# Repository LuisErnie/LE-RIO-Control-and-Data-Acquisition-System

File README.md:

# Industrial Control and Data Acquisition System

LOW-level Engineering modular data acquisition and control hardware platform. The system is a combination of a power supply, integrated I/O, integrated communications interfaces, signal and isolation to interface with expansion modules to tailor it to the application and an FPGA as a main controller.

The system is designed around the DE-10 Nano FPGA board from Terasic, although any embedded controller can be adapted to interface with the two 40-pin IDC connectors.

## Features
- Fully Modular I/O interface.
- Expansion Ports with 24V and 5V Power and Signal Isolation.
- Single 24V Power Supply Required.
- Multiple Communications Interfaces Supported, RS-485, CAN, RS-232, USB, SPI and I2C.

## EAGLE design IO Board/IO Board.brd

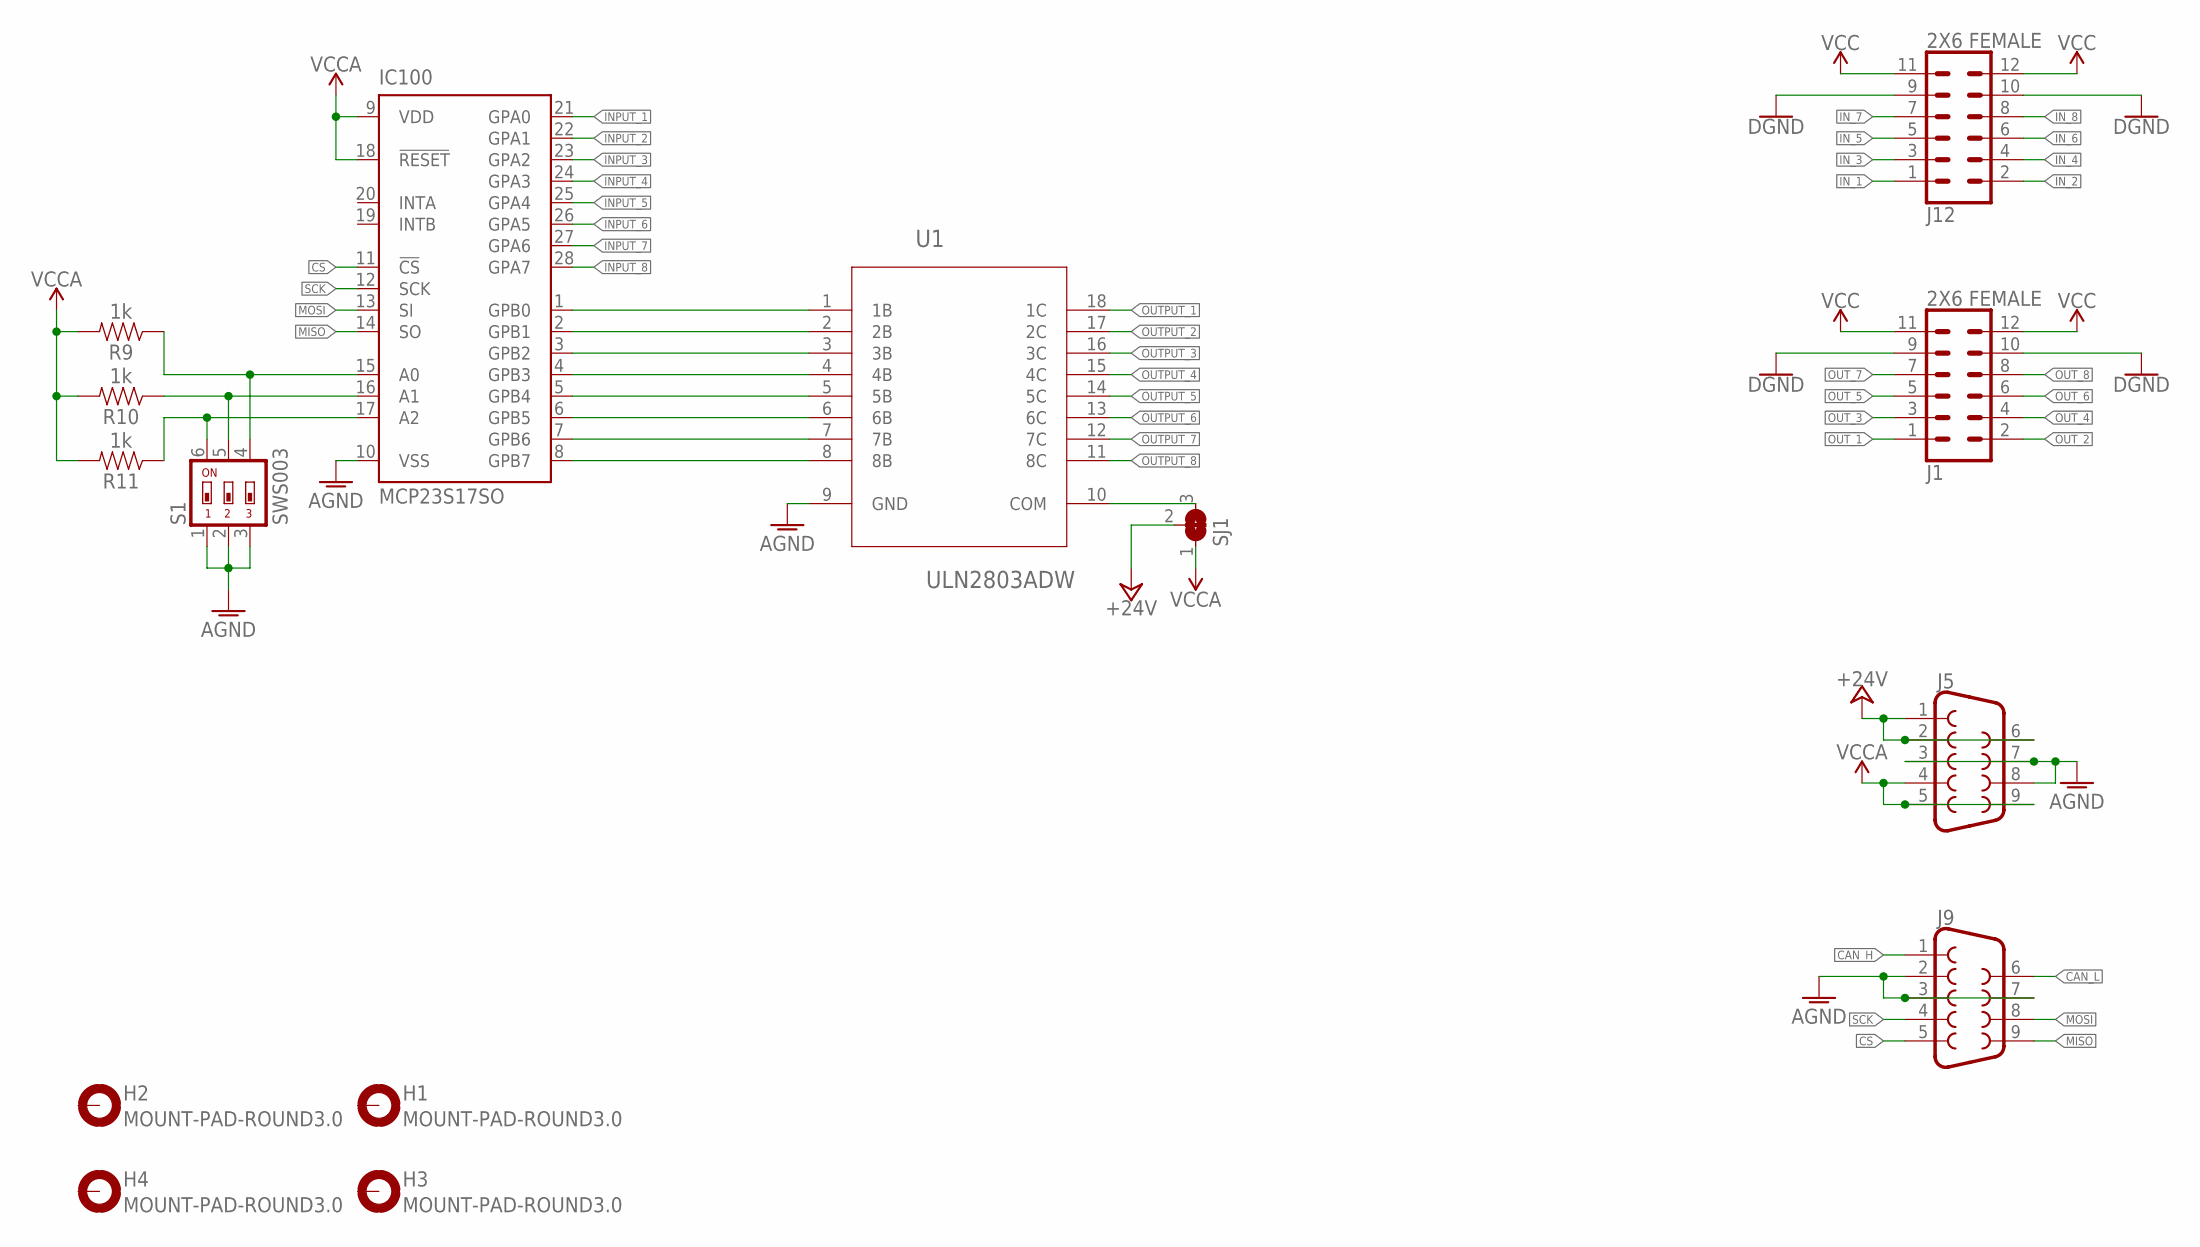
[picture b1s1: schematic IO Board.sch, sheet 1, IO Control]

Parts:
H1, H2, H3, H4: MOUNT-PAD-ROUND3.0; 3,0-PAD
IC100: MCP23S17SO; SO28W
J1, J12: 2X6 FEMALE; 2X6
J5, J9: DB9FEMALE; DB9
R9, R10, R11: 1k; 0805
S1: SWS003; SMS-003
SJ1: SOLDERJUMPER_2WAY; SOLDERJUMPER_2WAY_OPEN_NOPASTE
U1: ULN2803ADW; SOIC127P1030X265-18N

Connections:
+24V: J5.1, J5.2, J5.6, SJ1.2; also elsewhere on the board
AGND: IC100.10 (VSS), J5.3, J5.7, J5.8, J9.2, J9.3, J9.7, S1.1, S1.2, S1.3, U1.9 (GND); also elsewhere on the board
CAN_H: J9.1
CAN_L: J9.6
CS: IC100.11 (!CS), J9.5
GND: J1.9, J1.10, J12.9, J12.10; also elsewhere on the board
INPUT_1: IC100.21 (GPA0); also elsewhere on the board
INPUT_2: IC100.22 (GPA1); also elsewhere on the board
INPUT_3: IC100.23 (GPA2); also elsewhere on the board
INPUT_4: IC100.24 (GPA3); also elsewhere on the board
INPUT_5: IC100.25 (GPA4); also elsewhere on the board
INPUT_6: IC100.26 (GPA5); also elsewhere on the board
INPUT_7: IC100.27 (GPA6); also elsewhere on the board
INPUT_8: IC100.28 (GPA7); also elsewhere on the board
IN_1: J12.1; also elsewhere on the board
IN_2: J12.2; also elsewhere on the board
IN_3: J12.3; also elsewhere on the board
IN_4: J12.4; also elsewhere on the board
IN_5: J12.5; also elsewhere on the board
IN_6: J12.6; also elsewhere on the board
IN_7: J12.7; also elsewhere on the board
IN_8: J12.8; also elsewhere on the board
MISO: IC100.14 (SO), J9.9
MOSI: IC100.13 (SI), J9.8
unnamed: IC100.1 (GPB0), U1.1 (1B)
unnamed: IC100.3 (GPB2), U1.3 (3B)
unnamed: IC100.2 (GPB1), U1.2 (2B)
unnamed: IC100.4 (GPB3), U1.4 (4B)
unnamed: SJ1.3, U1.10 (COM)
unnamed: IC100.5 (GPB4), U1.5 (5B)
unnamed: IC100.7 (GPB6), U1.7 (7B)
unnamed: IC100.6 (GPB5), U1.6 (6B)
unnamed: IC100.8 (GPB7), U1.8 (8B)
unnamed: IC100.15 (A0), R9.1, S1.4
unnamed: IC100.16 (A1), R10.1, S1.5
unnamed: IC100.17 (A2), R11.1, S1.6
OUTPUT_1: U1.18 (1C); also elsewhere on the board
OUTPUT_2: U1.17 (2C); also elsewhere on the board
OUTPUT_3: U1.16 (3C); also elsewhere on the board
OUTPUT_4: U1.15 (4C); also elsewhere on the board
OUTPUT_5: U1.14 (5C); also elsewhere on the board
OUTPUT_6: U1.13 (6C); also elsewhere on the board
OUTPUT_7: U1.12 (7C); also elsewhere on the board
OUTPUT_8: U1.11 (8C); also elsewhere on the board
OUT_1: J1.1; also elsewhere on the board
OUT_2: J1.2; also elsewhere on the board
OUT_3: J1.3; also elsewhere on the board
OUT_4: J1.4; also elsewhere on the board
OUT_5: J1.5; also elsewhere on the board
OUT_6: J1.6; also elsewhere on the board
OUT_7: J1.7; also elsewhere on the board
OUT_8: J1.8; also elsewhere on the board
SCK: IC100.12 (SCK), J9.4
VCC: J1.11, J1.12, J12.11, J12.12; also elsewhere on the board
VCCA: IC100.9 (VDD), IC100.18 (!RESET), J5.4, J5.5, J5.9, R9.2, R10.2, R11.2, SJ1.1; also elsewhere on the board

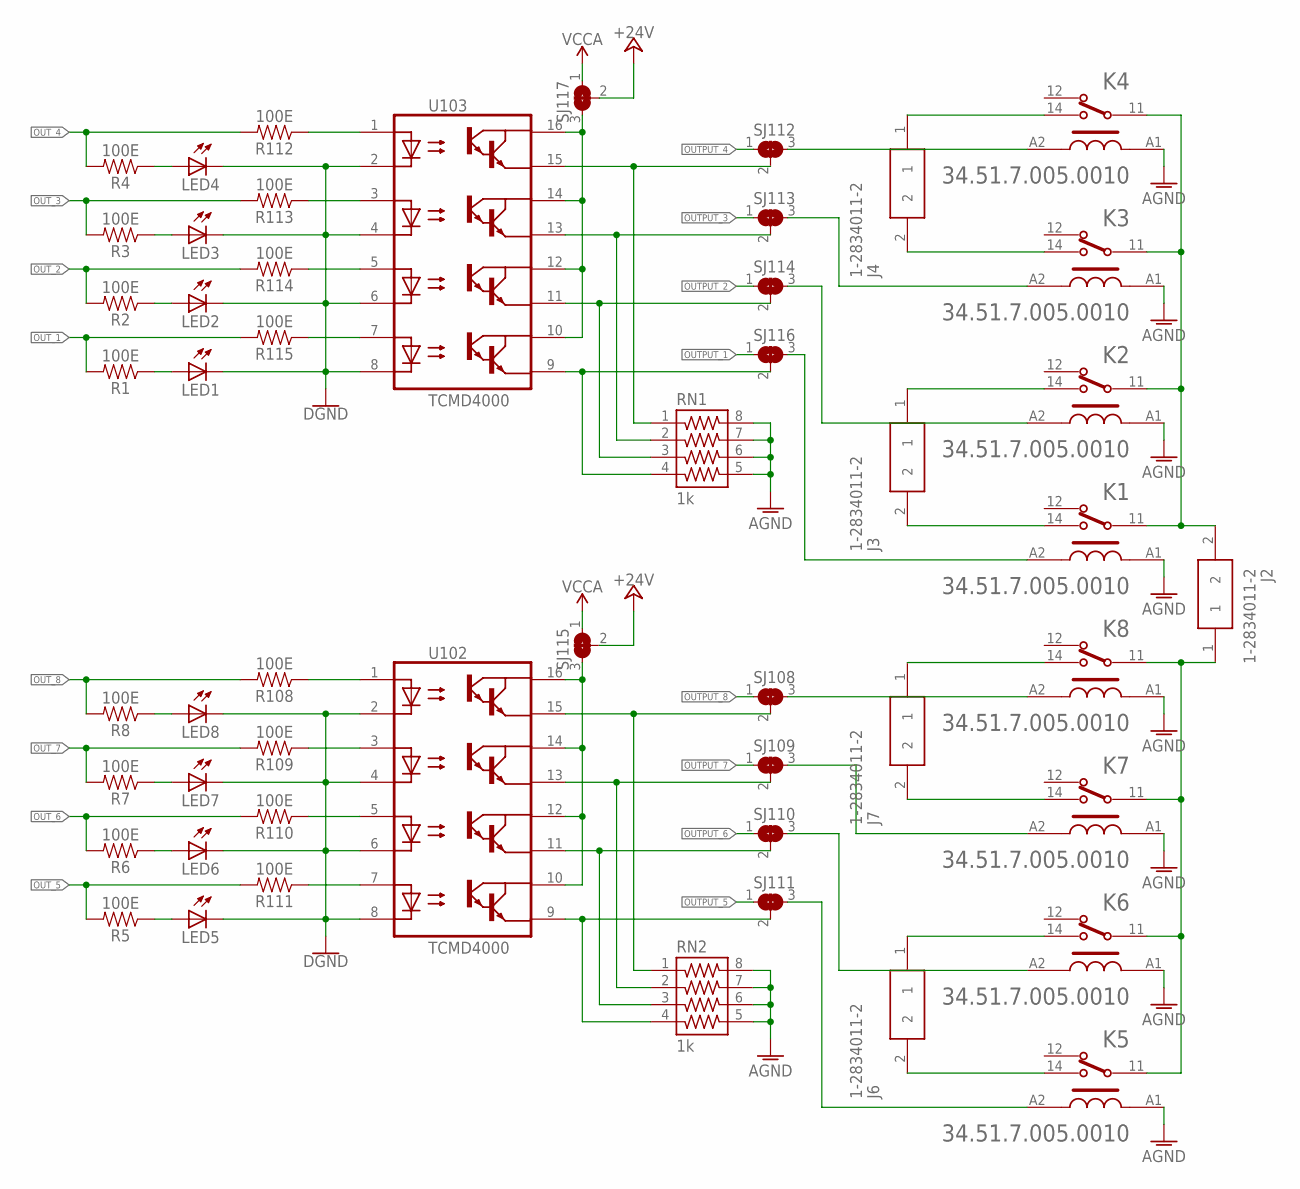
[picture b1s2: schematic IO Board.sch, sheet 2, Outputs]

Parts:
J2, J3, J4, J6, J7: 1-2834011-2; 128340112
K1, K2, K3, K4, K5, K6, K7, K8: FINDER_34.51.7.005.0010FINDER_34.51.7.005.0010_0_0; FINDER_34.51.7.005.0010_0
LED1, LED2, LED3, LED4, LED5, LED6, LED7, LED8: LEDCHIP-LED0805; CHIP-LED0805
R1, R2, R3, R4, R5, R6, R7, R8, R108, R109, R110, R111, R112, R113, R114, R115: 100E; 0805
RN1, RN2: 1k; 743-8NS
SJ108, SJ109, SJ110, SJ111, SJ112, SJ113, SJ114, SJ115, SJ116, SJ117: SOLDERJUMPER_2WAY; SOLDERJUMPER_2WAY_OPEN_NOPASTE
U102, U103: TCMD4000; SOIC127P686X201-16N

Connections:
+24V: SJ115.2, SJ117.2; also elsewhere on the board
AGND: K1.A1, K2.A1, K3.A1, K4.A1, K5.A1, K6.A1, K7.A1, K8.A1, RN1.5, RN1.6, RN1.7, RN1.8, RN2.5, RN2.6, RN2.7, RN2.8; also elsewhere on the board
GND: LED1.C, LED2.C, LED3.C, LED4.C, LED5.C, LED6.C, LED7.C, LED8.C, U102.2 (C1), U102.4 (C2), U102.6 (C3), U102.8 (C4), U103.2 (C1), U103.4 (C2), U103.6 (C3), U103.8 (C4); also elsewhere on the board
unnamed: K3.A2, SJ113.3
unnamed: RN1.3, SJ114.2, U103.11 (E3)
unnamed: RN1.4, SJ116.2, U103.9 (E4)
unnamed: K8.A2, SJ108.3
unnamed: K7.A2, SJ109.3
unnamed: RN2.3, SJ110.2, U102.11 (E3)
unnamed: RN2.4, SJ111.2, U102.9 (E4)
unnamed: K4.A2, SJ112.3
unnamed: LED4.A, R4.1
unnamed: LED8.A, R8.1
unnamed: LED7.A, R7.1
unnamed: LED6.A, R6.1
unnamed: LED5.A, R5.1
unnamed: R108.1, U102.1 (A1)
unnamed: R109.1, U102.3 (A2)
unnamed: R110.1, U102.5 (A3)
unnamed: R111.1, U102.7 (A4)
unnamed: SJ115.3, U102.10 (CO4), U102.12 (CO3), U102.14 (CO2), U102.16 (CO1)
unnamed: RN2.2, SJ109.2, U102.13 (E2)
unnamed: LED3.A, R3.1
unnamed: RN2.1, SJ108.2, U102.15 (E1)
unnamed: K5.A2, SJ111.3
unnamed: J4.1, K4.14
unnamed: J4.2, K3.14
unnamed: J3.1, K2.14
unnamed: LED2.A, R2.1
unnamed: LED1.A, R1.1
unnamed: J3.2, K1.14
unnamed: J2.1, K5.11, K6.11, K7.11, K8.11
unnamed: R112.1, U103.1 (A1)
unnamed: J7.1, K8.14
unnamed: J2.2, K1.11, K2.11, K3.11, K4.11
unnamed: K6.A2, SJ110.3
unnamed: J7.2, K7.14
unnamed: J6.1, K6.14
unnamed: K2.A2, SJ114.3
unnamed: R113.1, U103.3 (A2)
unnamed: R114.1, U103.5 (A3)
unnamed: R115.1, U103.7 (A4)
unnamed: SJ117.3, U103.10 (CO4), U103.12 (CO3), U103.14 (CO2), U103.16 (CO1)
unnamed: RN1.2, SJ113.2, U103.13 (E2)
unnamed: RN1.1, SJ112.2, U103.15 (E1)
unnamed: K1.A2, SJ116.3
unnamed: J6.2, K5.14
OUTPUT_1: SJ116.1; also elsewhere on the board
OUTPUT_2: SJ114.1; also elsewhere on the board
OUTPUT_3: SJ113.1; also elsewhere on the board
OUTPUT_4: SJ112.1; also elsewhere on the board
OUTPUT_5: SJ111.1; also elsewhere on the board
OUTPUT_6: SJ110.1; also elsewhere on the board
OUTPUT_7: SJ109.1; also elsewhere on the board
OUTPUT_8: SJ108.1; also elsewhere on the board
OUT_1: R1.2, R115.2; also elsewhere on the board
OUT_2: R2.2, R114.2; also elsewhere on the board
OUT_3: R3.2, R113.2; also elsewhere on the board
OUT_4: R4.2, R112.2; also elsewhere on the board
OUT_5: R5.2, R111.2; also elsewhere on the board
OUT_6: R6.2, R110.2; also elsewhere on the board
OUT_7: R7.2, R109.2; also elsewhere on the board
OUT_8: R8.2, R108.2; also elsewhere on the board
VCCA: SJ115.1, SJ117.1; also elsewhere on the board

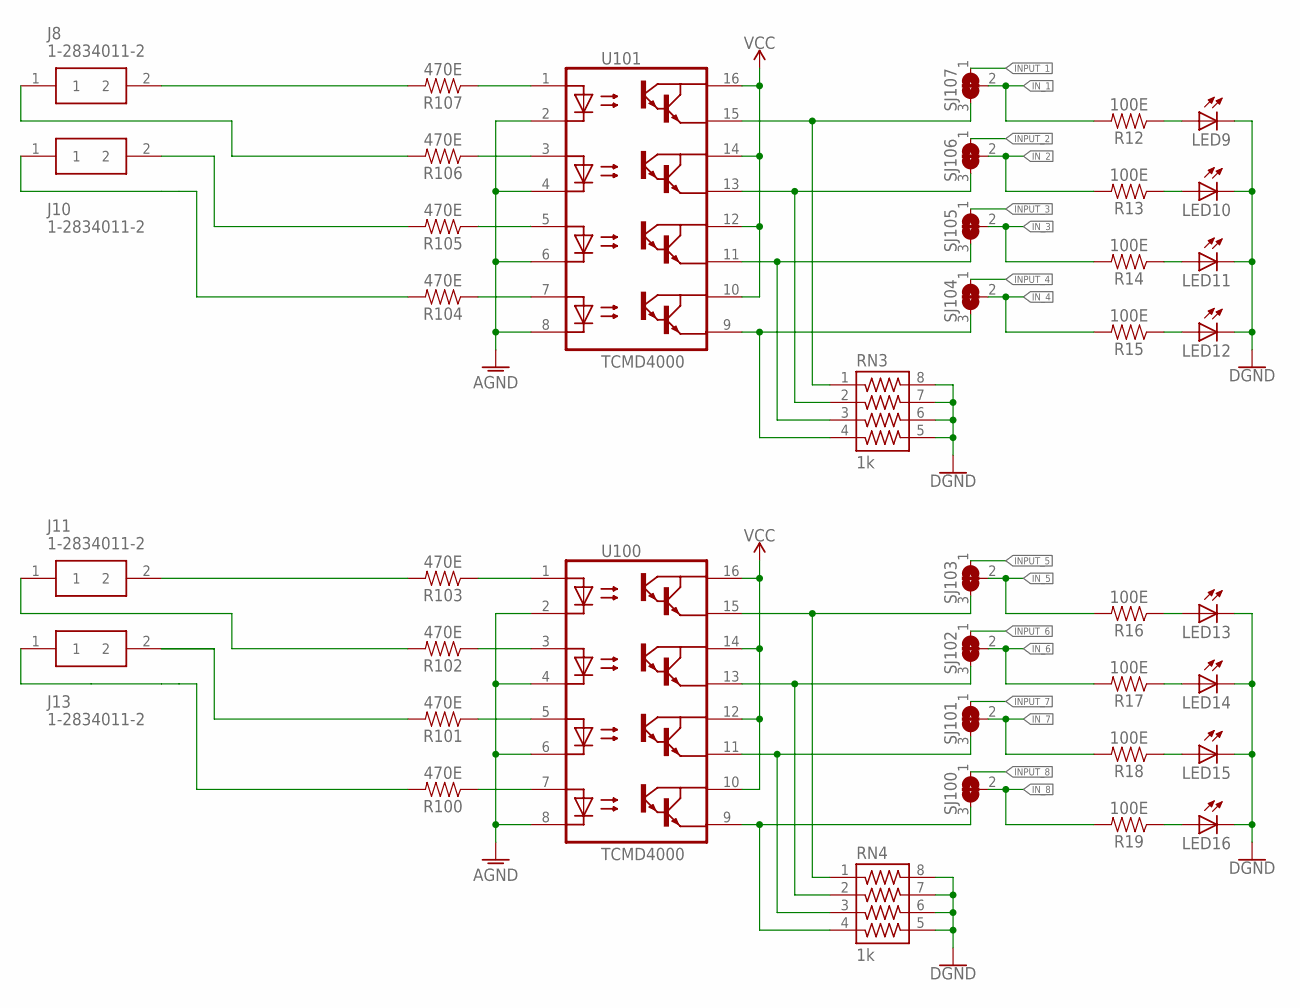
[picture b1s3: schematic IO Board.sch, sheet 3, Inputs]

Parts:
J8, J10, J11, J13: 1-2834011-2; 128340112
LED9, LED10, LED11, LED12, LED13, LED14, LED15, LED16: LEDCHIP-LED0805; CHIP-LED0805
R12, R13, R14, R15, R16, R17, R18, R19: 100E; 0805
R100, R101, R102, R103, R104, R105, R106, R107: 470E; 0805
RN3, RN4: 1k; 743-8NS
SJ100, SJ101, SJ102, SJ103, SJ104, SJ105, SJ106, SJ107: SOLDERJUMPER_2WAY; SOLDERJUMPER_2WAY_OPEN_NOPASTE
U100, U101: TCMD4000; SOIC127P686X201-16N

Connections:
AGND: U100.2 (C1), U100.4 (C2), U100.6 (C3), U100.8 (C4), U101.2 (C1), U101.4 (C2), U101.6 (C3), U101.8 (C4); also elsewhere on the board
GND: LED9.C, LED10.C, LED11.C, LED12.C, LED13.C, LED14.C, LED15.C, LED16.C, RN3.5, RN3.6, RN3.7, RN3.8, RN4.5, RN4.6, RN4.7, RN4.8; also elsewhere on the board
INPUT_1: SJ107.1; also elsewhere on the board
INPUT_2: SJ106.1; also elsewhere on the board
INPUT_3: SJ105.1; also elsewhere on the board
INPUT_4: SJ104.1; also elsewhere on the board
INPUT_5: SJ103.1; also elsewhere on the board
INPUT_6: SJ102.1; also elsewhere on the board
INPUT_7: SJ101.1; also elsewhere on the board
INPUT_8: SJ100.1; also elsewhere on the board
IN_1: R12.2, SJ107.2; also elsewhere on the board
IN_2: R13.2, SJ106.2; also elsewhere on the board
IN_3: R14.2, SJ105.2; also elsewhere on the board
IN_4: R15.2, SJ104.2; also elsewhere on the board
IN_5: R16.2, SJ103.2; also elsewhere on the board
IN_6: R17.2, SJ102.2; also elsewhere on the board
IN_7: R18.2, SJ101.2; also elsewhere on the board
IN_8: R19.2, SJ100.2; also elsewhere on the board
unnamed: LED9.A, R12.1
unnamed: LED10.A, R13.1
unnamed: LED11.A, R14.1
unnamed: LED12.A, R15.1
unnamed: R107.1, U101.1 (A1)
unnamed: R106.1, U101.3 (A2)
unnamed: J8.1, R106.2
unnamed: J13.2, R101.2
unnamed: R105.1, U101.5 (A3)
unnamed: R104.1, U101.7 (A4)
unnamed: LED13.A, R16.1
unnamed: RN3.2, SJ106.3, U101.13 (E2)
unnamed: RN3.1, SJ107.3, U101.15 (E1)
unnamed: LED14.A, R17.1
unnamed: LED15.A, R18.1
unnamed: LED16.A, R19.1
unnamed: R103.1, U100.1 (A1)
unnamed: R102.1, U100.3 (A2)
unnamed: R101.1, U100.5 (A3)
unnamed: R100.1, U100.7 (A4)
unnamed: RN4.2, SJ102.3, U100.13 (E2)
unnamed: RN4.1, SJ103.3, U100.15 (E1)
unnamed: RN4.3, SJ101.3, U100.11 (E3)
unnamed: RN4.4, SJ100.3, U100.9 (E4)
unnamed: J8.2, R107.2
unnamed: J10.2, R105.2
unnamed: J10.1, R104.2
unnamed: RN3.3, SJ105.3, U101.11 (E3)
unnamed: RN3.4, SJ104.3, U101.9 (E4)
unnamed: J11.2, R103.2
unnamed: J11.1, R102.2
unnamed: J13.1, R100.2
VCC: U100.10 (CO4), U100.12 (CO3), U100.14 (CO2), U100.16 (CO1), U101.10 (CO4), U101.12 (CO3), U101.14 (CO2), U101.16 (CO1); also elsewhere on the board

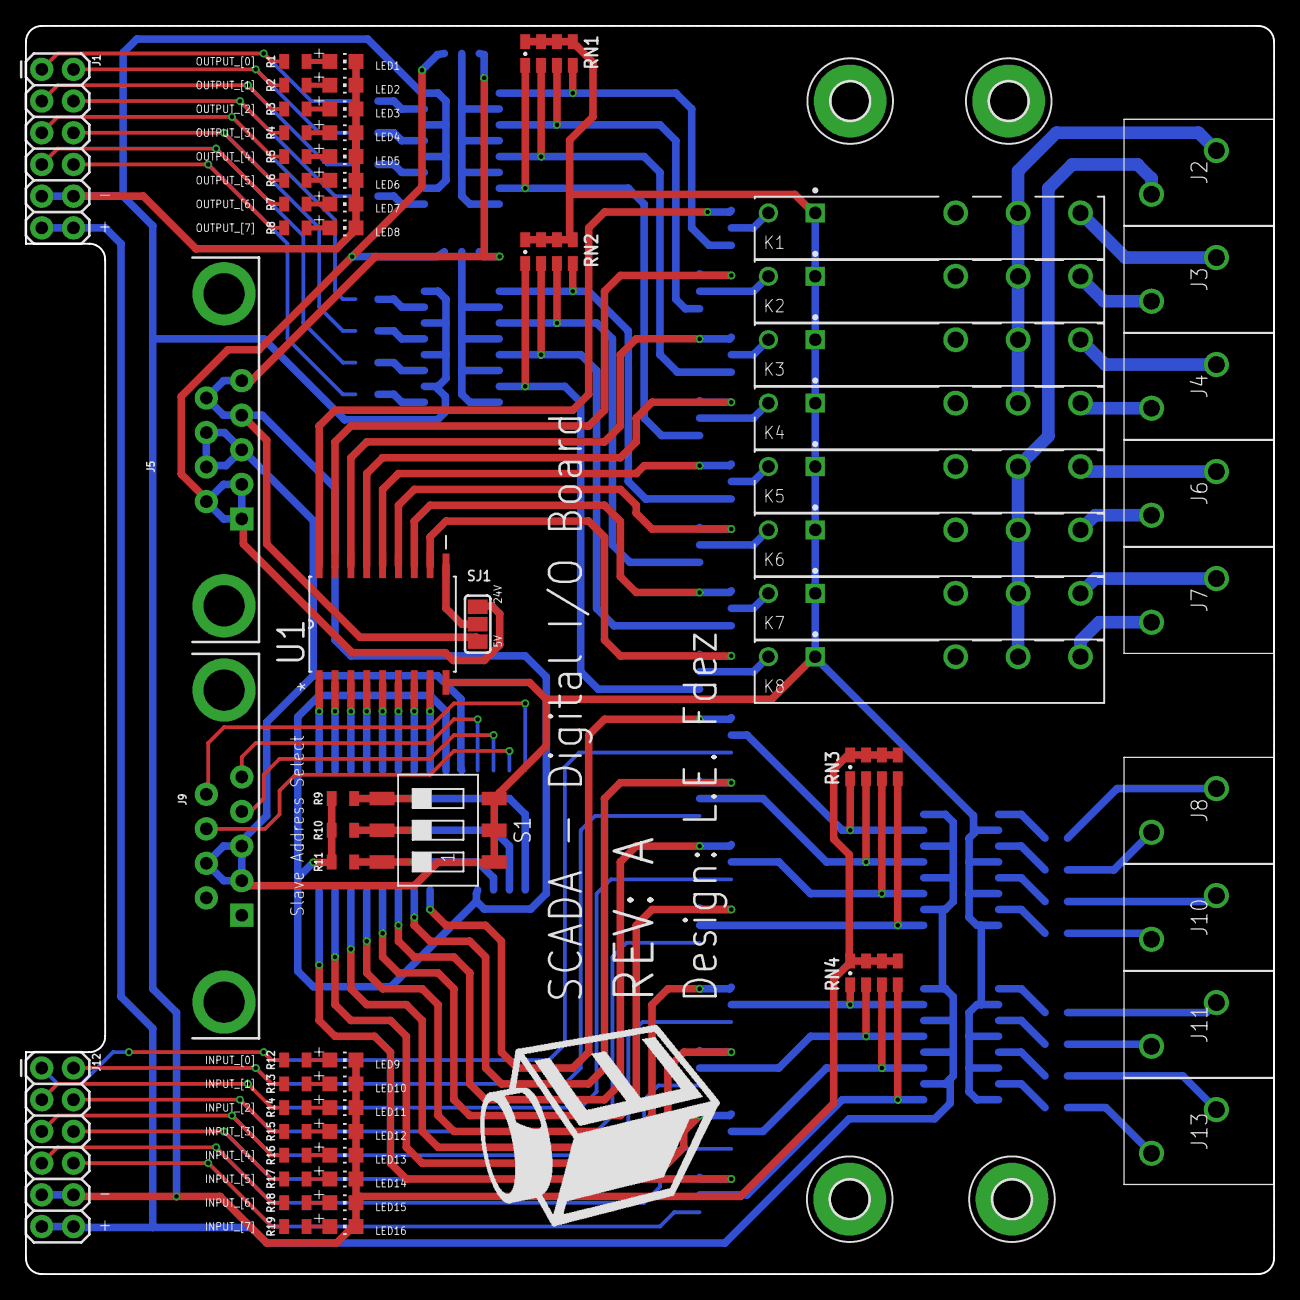
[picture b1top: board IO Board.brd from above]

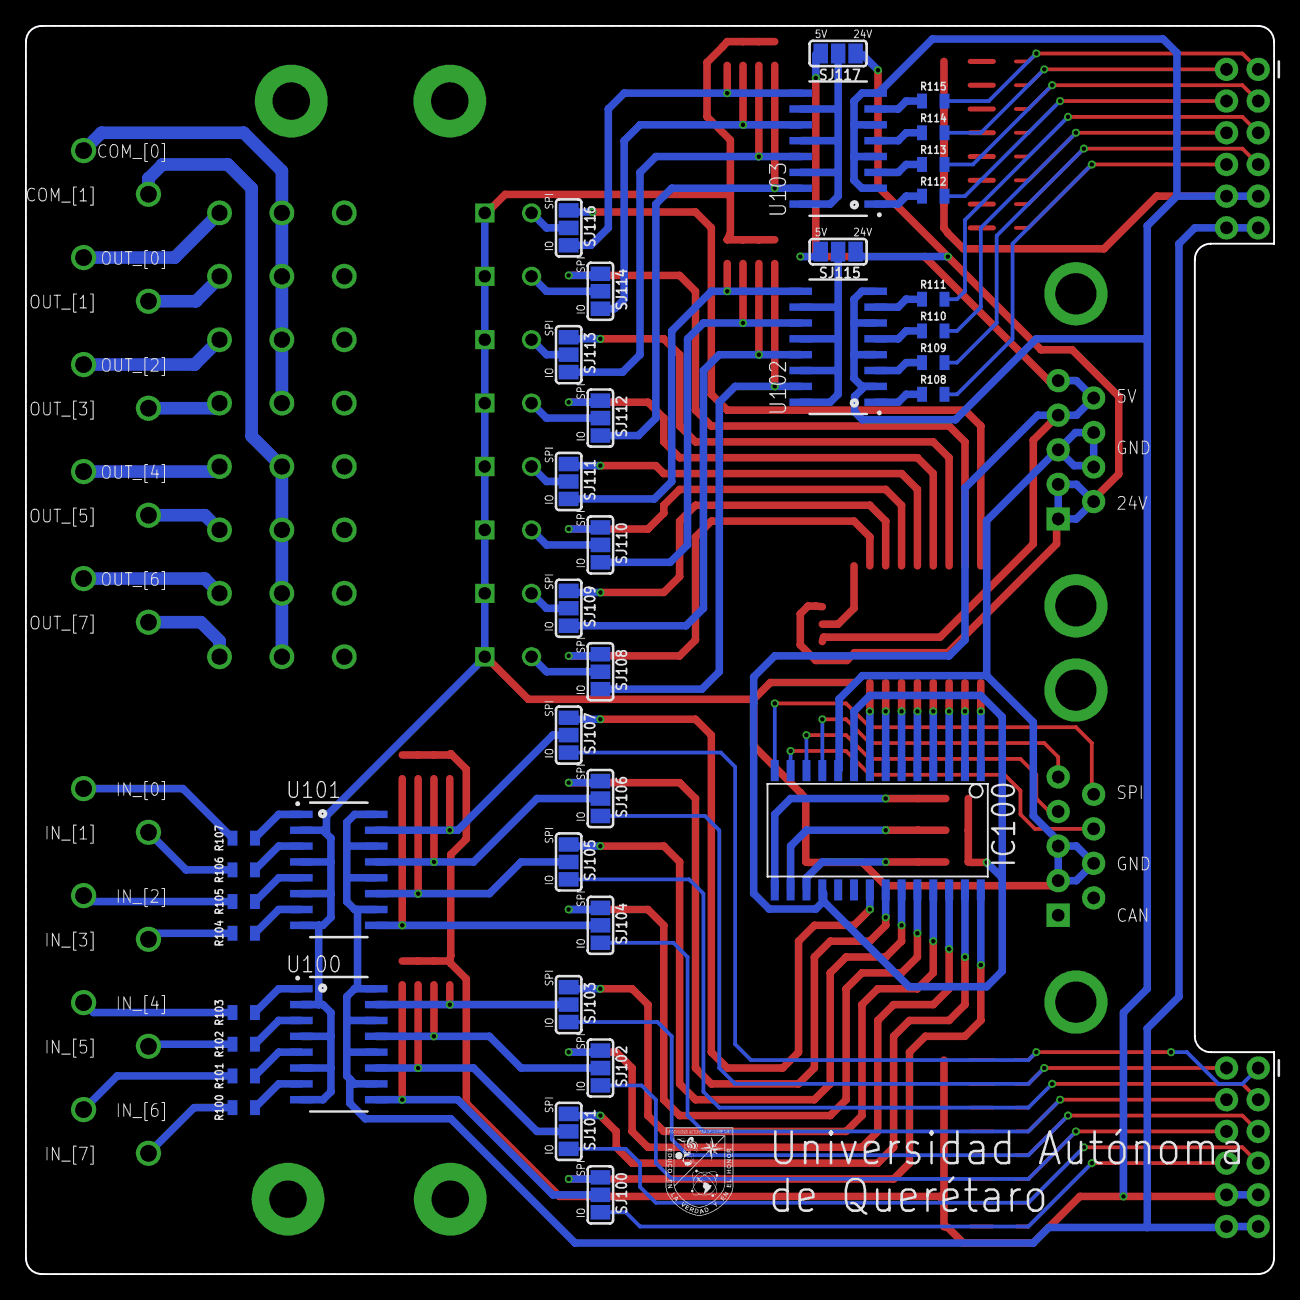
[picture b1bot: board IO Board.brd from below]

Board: 2 copper layers, 100.0 x 100.0 mm, 106 parts (39 on the bottom side), 129 nets.

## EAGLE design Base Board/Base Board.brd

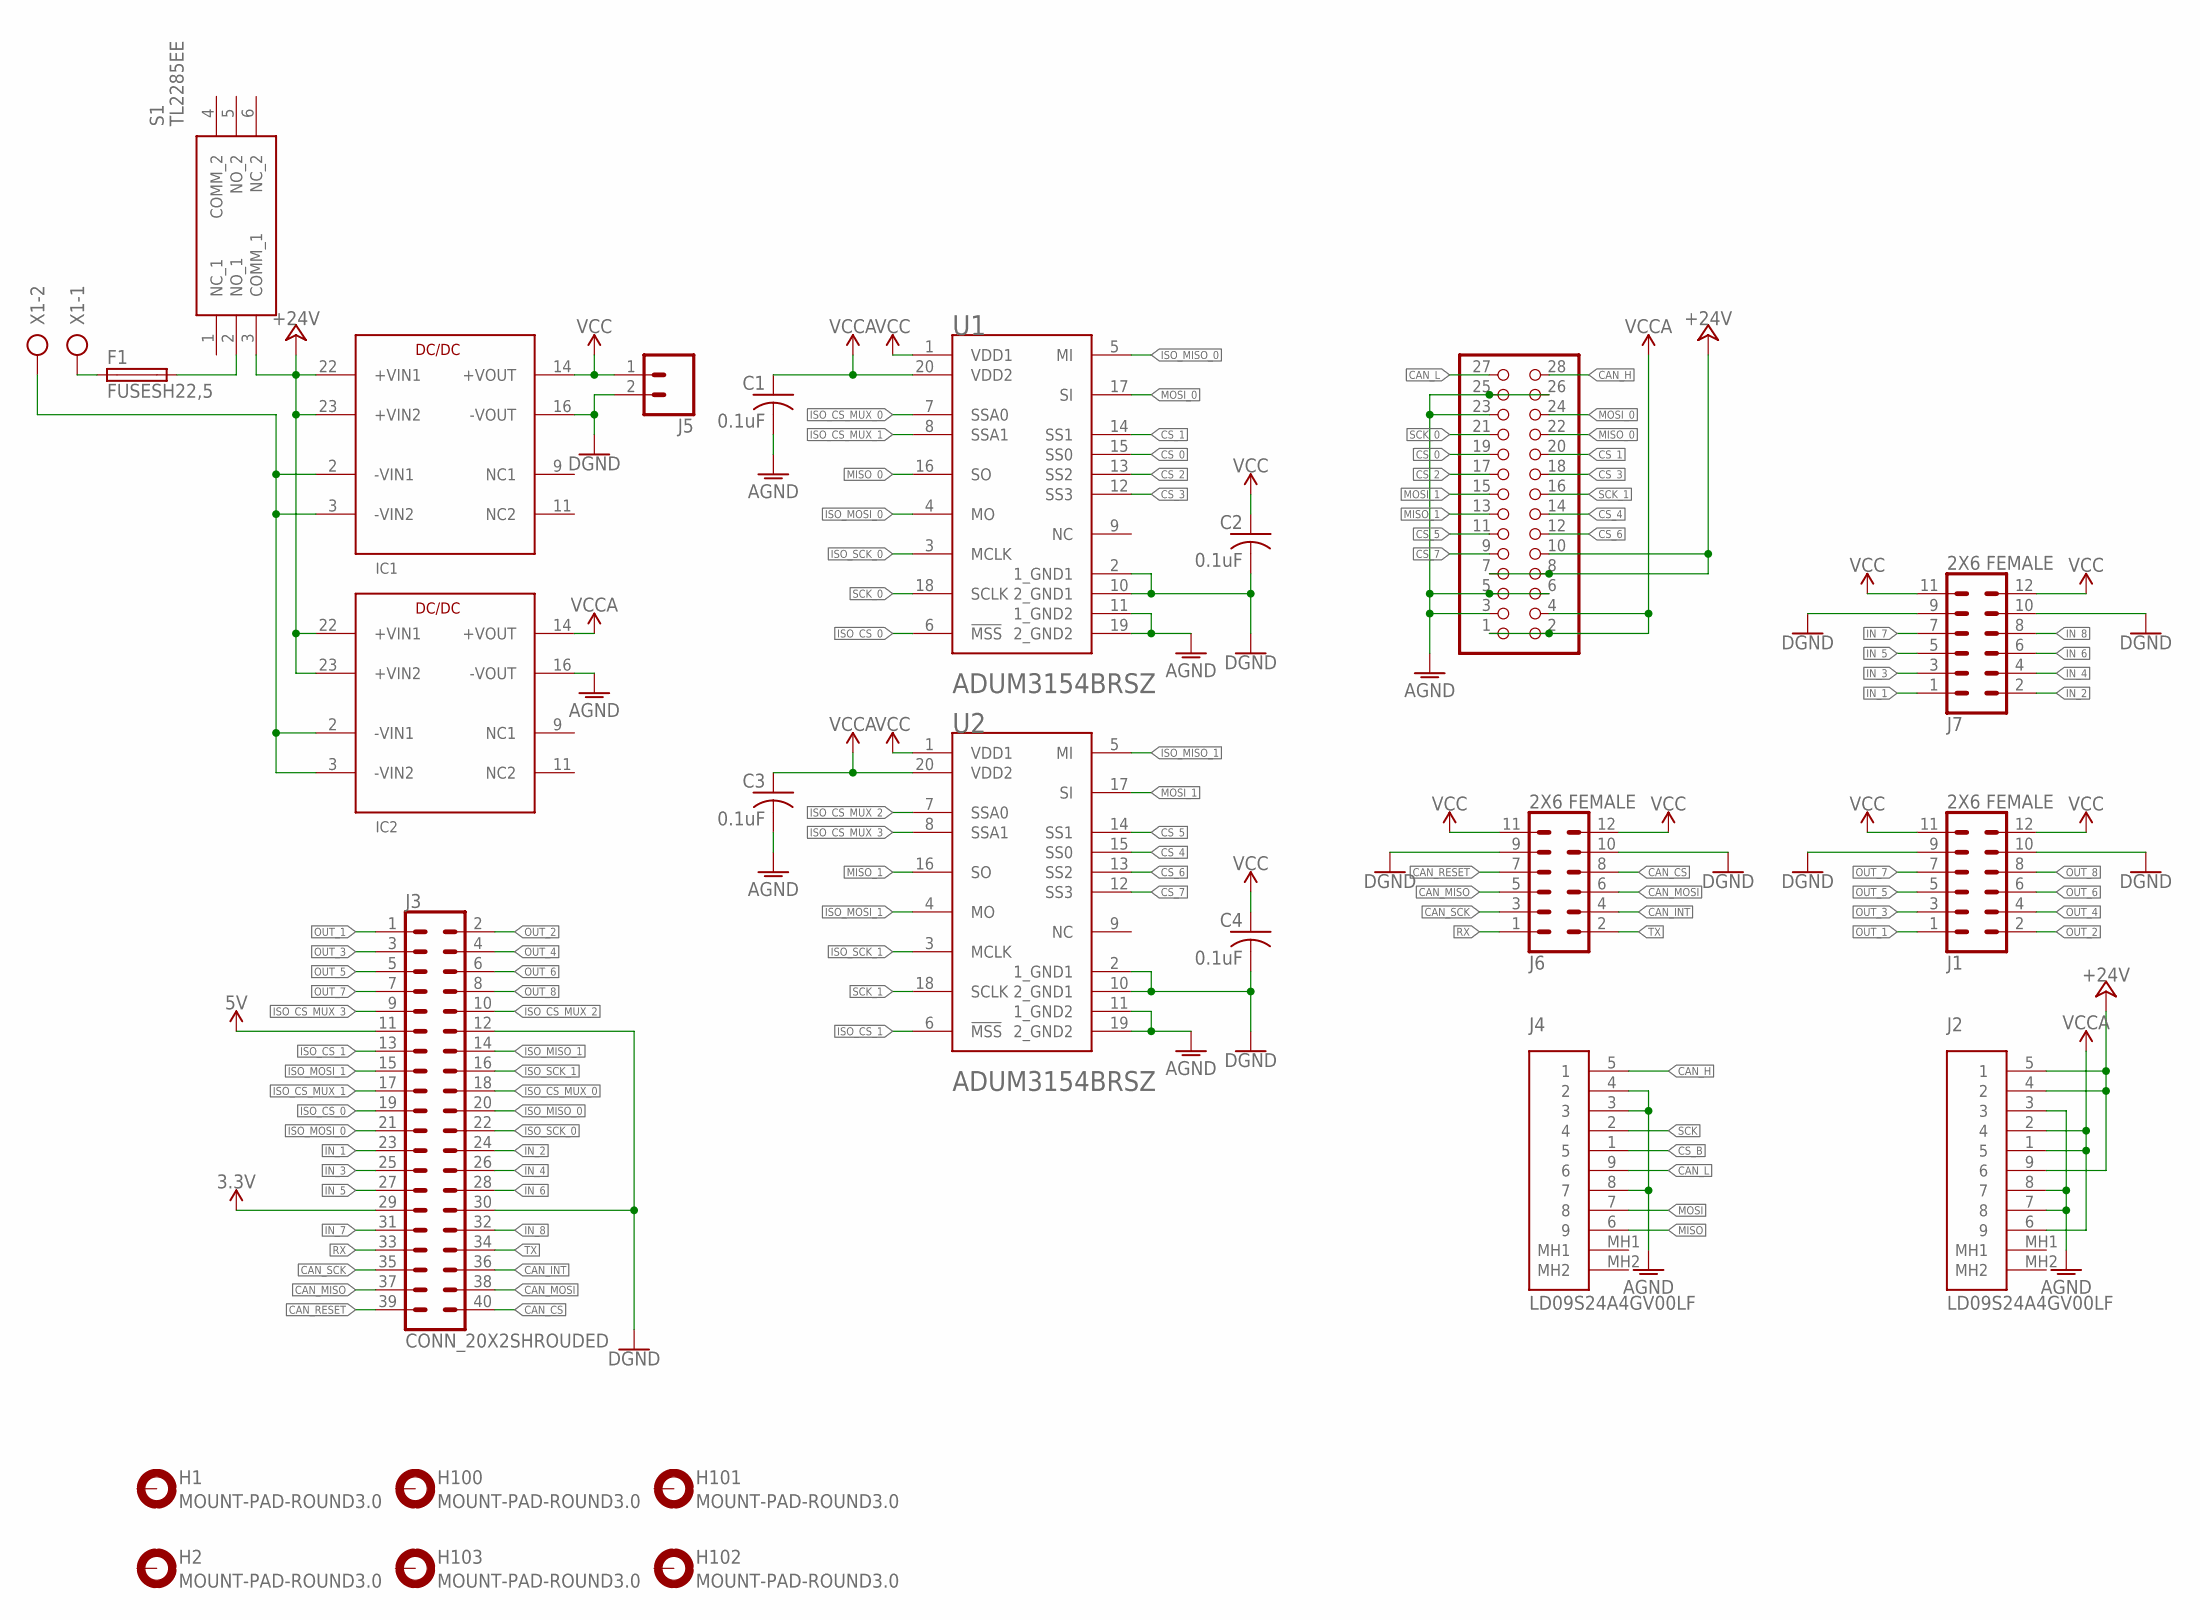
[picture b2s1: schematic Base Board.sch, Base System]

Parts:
C1, C2, C3, C4: 0.1uF; C0805
F1: FUSESH22,5; SH22,5
H1, H2, H100, H101, H102, H103: MOUNT-PAD-ROUND3.0; 3,0-PAD
IC1, IC2: TEL_5_SERIES
J1, J6, J7: 2X6 FEMALE; 2X6
J2, J4: LD09S24A4GV00LF
J3: CONN_20X2SHROUDED; 2X20_SHROUDED
J5: CONN_02POLAR_LOCK; MOLEX-1X2_LOCK
JP1: PINHD-2X14/90; 2X14/90
S1: TL2285EE
U1, U2: ANALOG_DEVICES_INC_ADUM3154BRSZANALOG_DEVICES_INC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; ANALOG_DEVICES_INC_ADUM3154BRSZ_0
X1: AK500/2-H

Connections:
3.3V: J3.29
5V: J3.11
+24V: IC1.22 (+VIN1), IC1.23 (+VIN2), IC2.22 (+VIN1), IC2.23 (+VIN2), J2.4 (2), J2.5 (1), J2.9 (6), JP1.7, JP1.8, JP1.10, S1.3 (COMM_1)
AGND: C1.2, C3.2, IC2.16 (-VOUT), J2.3, J2.7 (8), J2.8 (7), J4.3, J4.4 (2), J4.8 (7), JP1.3, JP1.5, JP1.6, JP1.23, JP1.25, JP1.26, U1.11 (1_GND2), U1.19 (2_GND2), U2.11 (1_GND2), U2.19 (2_GND2)
CAN_CS: J3.40, J6.8
CAN_H: J4.5 (1), JP1.28
CAN_INT: J3.36, J6.4
CAN_L: J4.9 (6), JP1.27
CAN_MISO: J3.37, J6.5
CAN_MOSI: J3.38, J6.6
CAN_RESET: J3.39, J6.7
CAN_SCK: J3.35, J6.3
CS_0: JP1.19, U1.15 (SS0)
CS_1: JP1.20, U1.14 (SS1)
CS_2: JP1.17, U1.13 (SS2)
CS_3: JP1.18, U1.12 (SS3)
CS_4: JP1.14, U2.15 (SS0)
CS_5: JP1.11, U2.14 (SS1)
CS_6: JP1.12, U2.13 (SS2)
CS_7: JP1.9, U2.12 (SS3)
CS_B: J4.1 (5)
GND: C2.2, C4.2, IC1.16 (-VOUT), J1.9, J1.10, J3.12, J3.30, J5.2, J6.9, J6.10, J7.9, J7.10, U1.2 (1_GND1), U1.10 (2_GND1), U2.2 (1_GND1), U2.10 (2_GND1)
IN_1: J3.23, J7.1
IN_2: J3.24, J7.2
IN_3: J3.25, J7.3
IN_4: J3.26, J7.4
IN_5: J3.27, J7.5
IN_6: J3.28, J7.6
IN_7: J3.31, J7.7
IN_8: J3.32, J7.8
ISO_CS_0: J3.19, U1.6 (!MSS!)
ISO_CS_1: J3.13, U2.6 (!MSS!)
ISO_CS_MUX_0: J3.18, U1.7 (SSA0)
ISO_CS_MUX_1: J3.17, U1.8 (SSA1)
ISO_CS_MUX_2: J3.10, U2.7 (SSA0)
ISO_CS_MUX_3: J3.9, U2.8 (SSA1)
ISO_MISO_0: J3.20, U1.5 (MI)
ISO_MISO_1: J3.14, U2.5 (MI)
ISO_MOSI_0: J3.21, U1.4 (MO)
ISO_MOSI_1: J3.15, U2.4 (MO)
ISO_SCK_0: J3.22, U1.3 (MCLK)
ISO_SCK_1: J3.16, U2.3 (MCLK)
MISO: J4.6 (9)
MISO_0: JP1.22, U1.16 (SO)
MISO_1: JP1.13, U2.16 (SO)
MOSI: J4.7 (8)
MOSI_0: JP1.24, U1.17 (SI)
MOSI_1: JP1.15, U2.17 (SI)
unnamed: IC1.2 (-VIN1), IC1.3 (-VIN2), IC2.2 (-VIN1), IC2.3 (-VIN2), X1.2
unnamed: F1.1, X1.1
unnamed: F1.2, S1.2 (NO_1)
OUT_1: J1.1, J3.1
OUT_2: J1.2, J3.2
OUT_3: J1.3, J3.3
OUT_4: J1.4, J3.4
OUT_5: J1.5, J3.5
OUT_6: J1.6, J3.6
OUT_7: J1.7, J3.7
OUT_8: J1.8, J3.8
RX: J3.33, J6.1
SCK: J4.2 (4)
SCK_0: JP1.21, U1.18 (SCLK)
SCK_1: JP1.16, U2.18 (SCLK)
TX: J3.34, J6.2
VCC: C2.1, C4.1, IC1.14 (+VOUT), J1.11, J1.12, J5.1, J6.11, J6.12, J7.11, J7.12, U1.1 (VDD1), U2.1 (VDD1)
VCCA: C1.1, C3.1, IC2.14 (+VOUT), J2.1 (5), J2.2 (4), J2.6 (9), JP1.1, JP1.2, JP1.4, U1.20 (VDD2), U2.20 (VDD2)

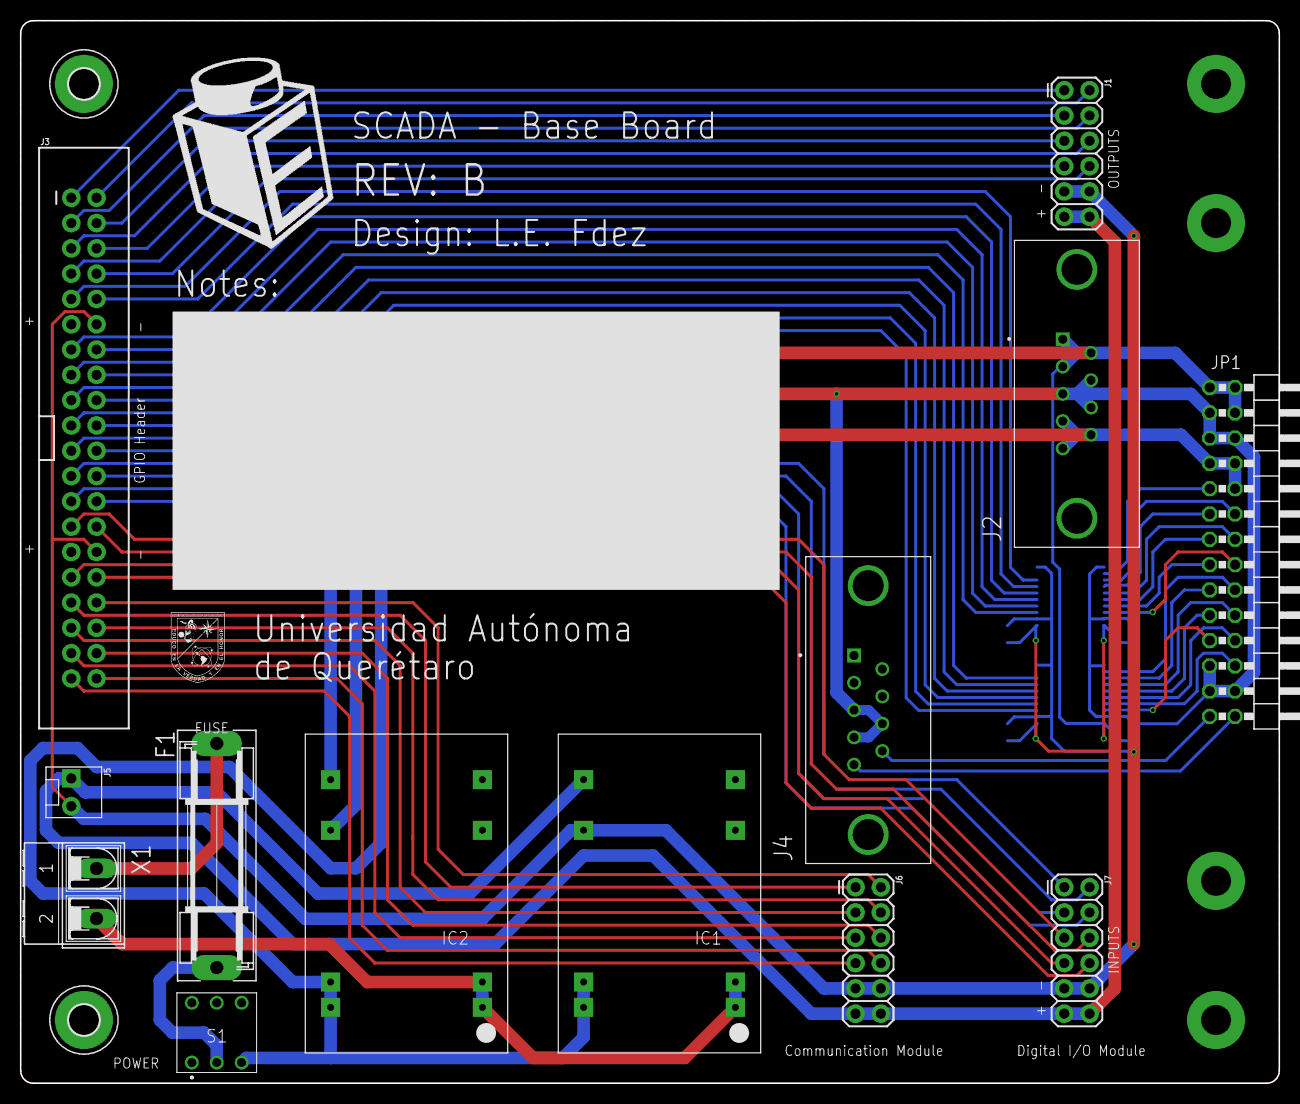
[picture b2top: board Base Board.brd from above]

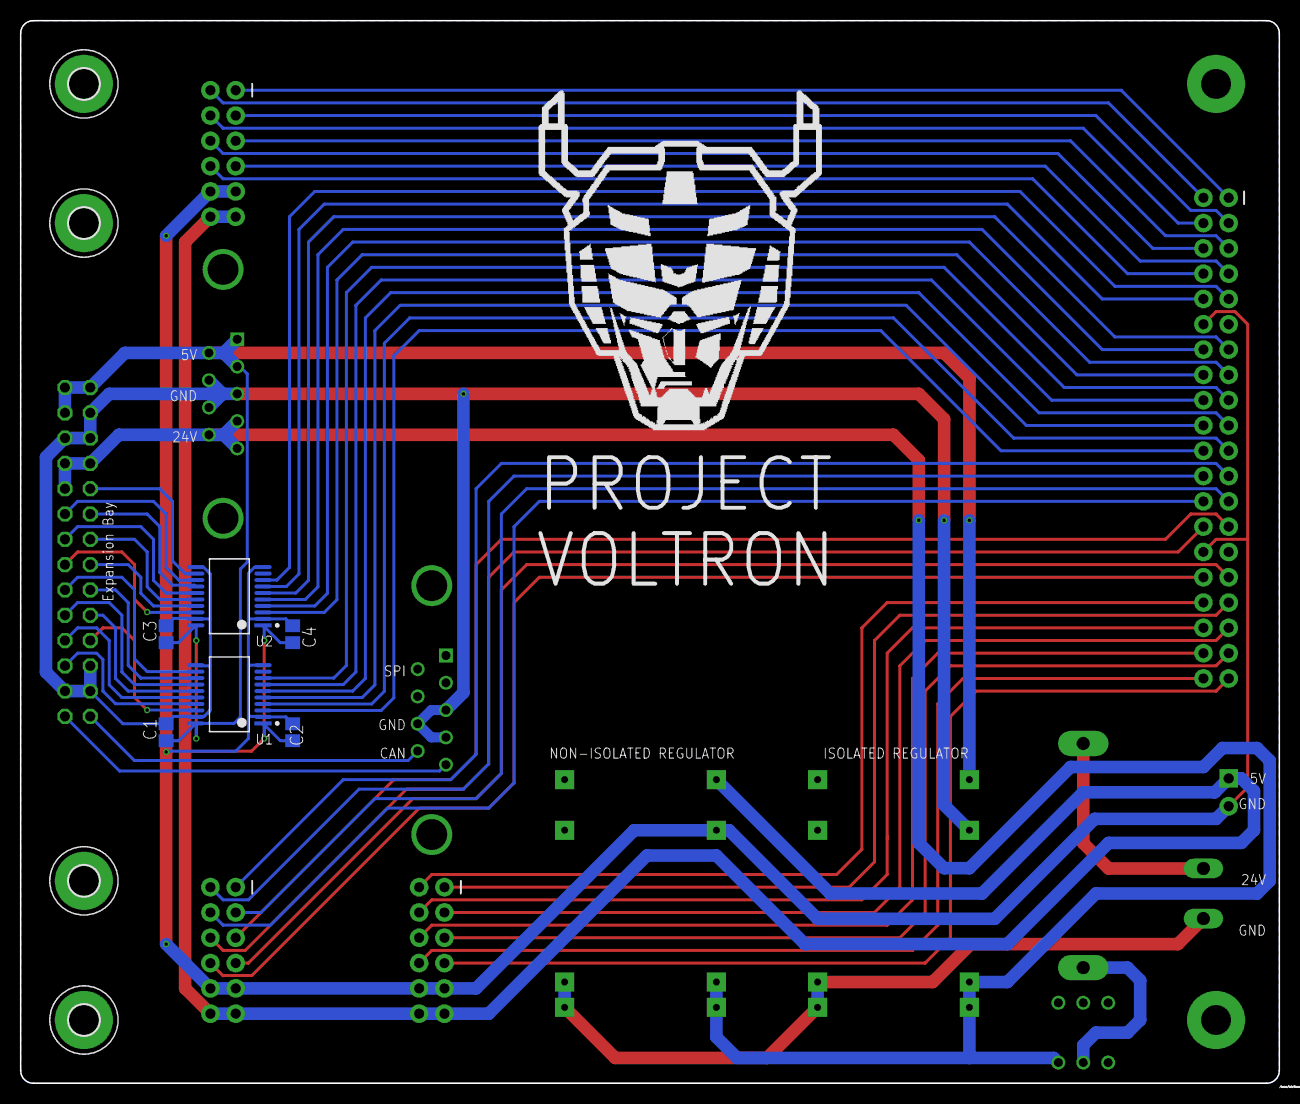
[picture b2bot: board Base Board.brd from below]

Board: 2 copper layers, 126.4 x 106.7 mm, 25 parts (10 on the bottom side), 60 nets.

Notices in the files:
parts and their libraries:
SparkFun-Connectors: Licensing: Creative Commons ShareAlike 4.0 International - https://creativecommons.org/licenses/by-sa/4.0
resistor-array: Copyright (C) 2008, Bob Starr
